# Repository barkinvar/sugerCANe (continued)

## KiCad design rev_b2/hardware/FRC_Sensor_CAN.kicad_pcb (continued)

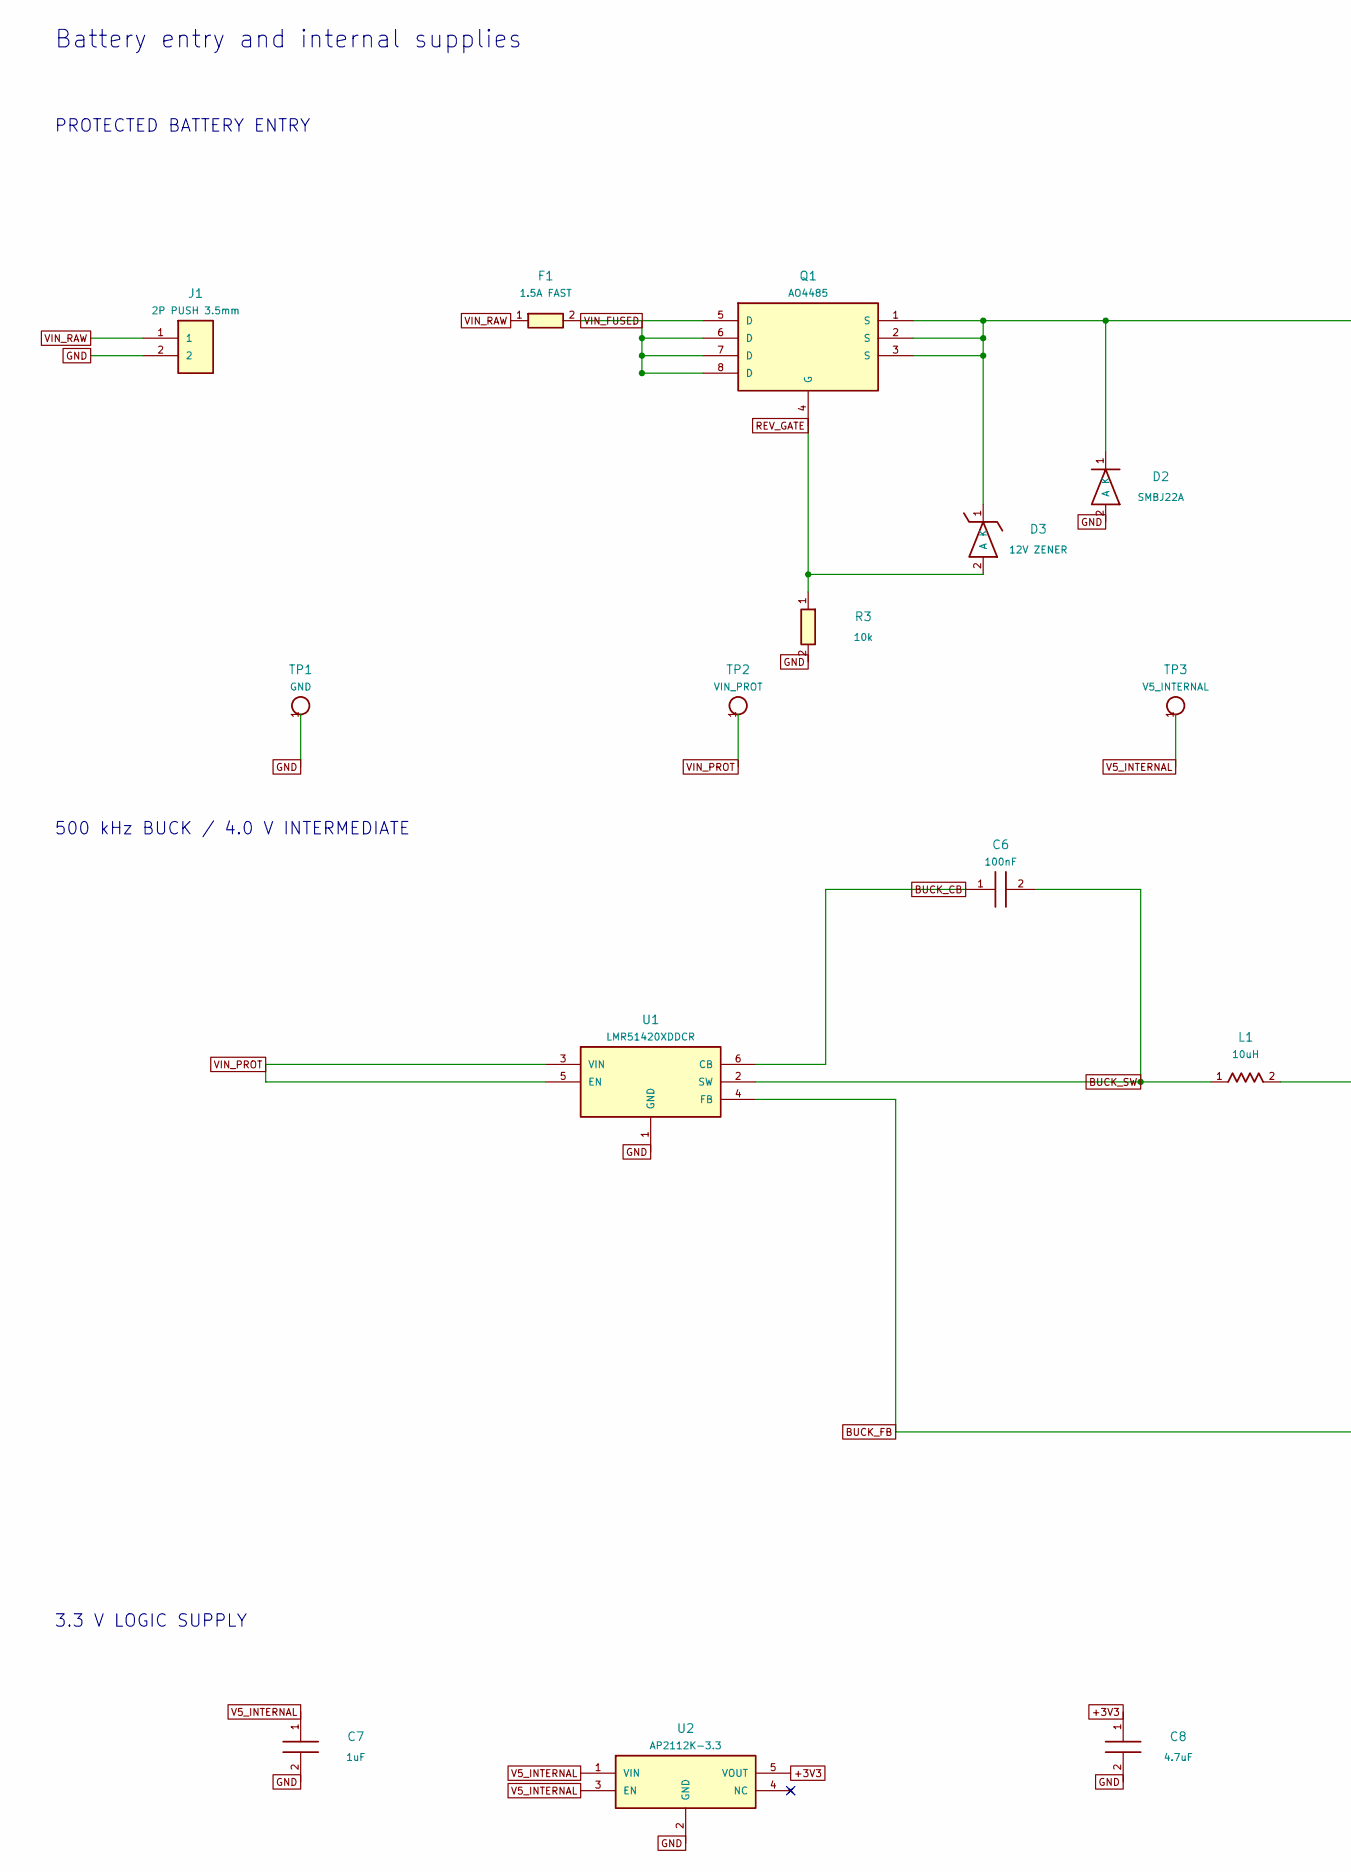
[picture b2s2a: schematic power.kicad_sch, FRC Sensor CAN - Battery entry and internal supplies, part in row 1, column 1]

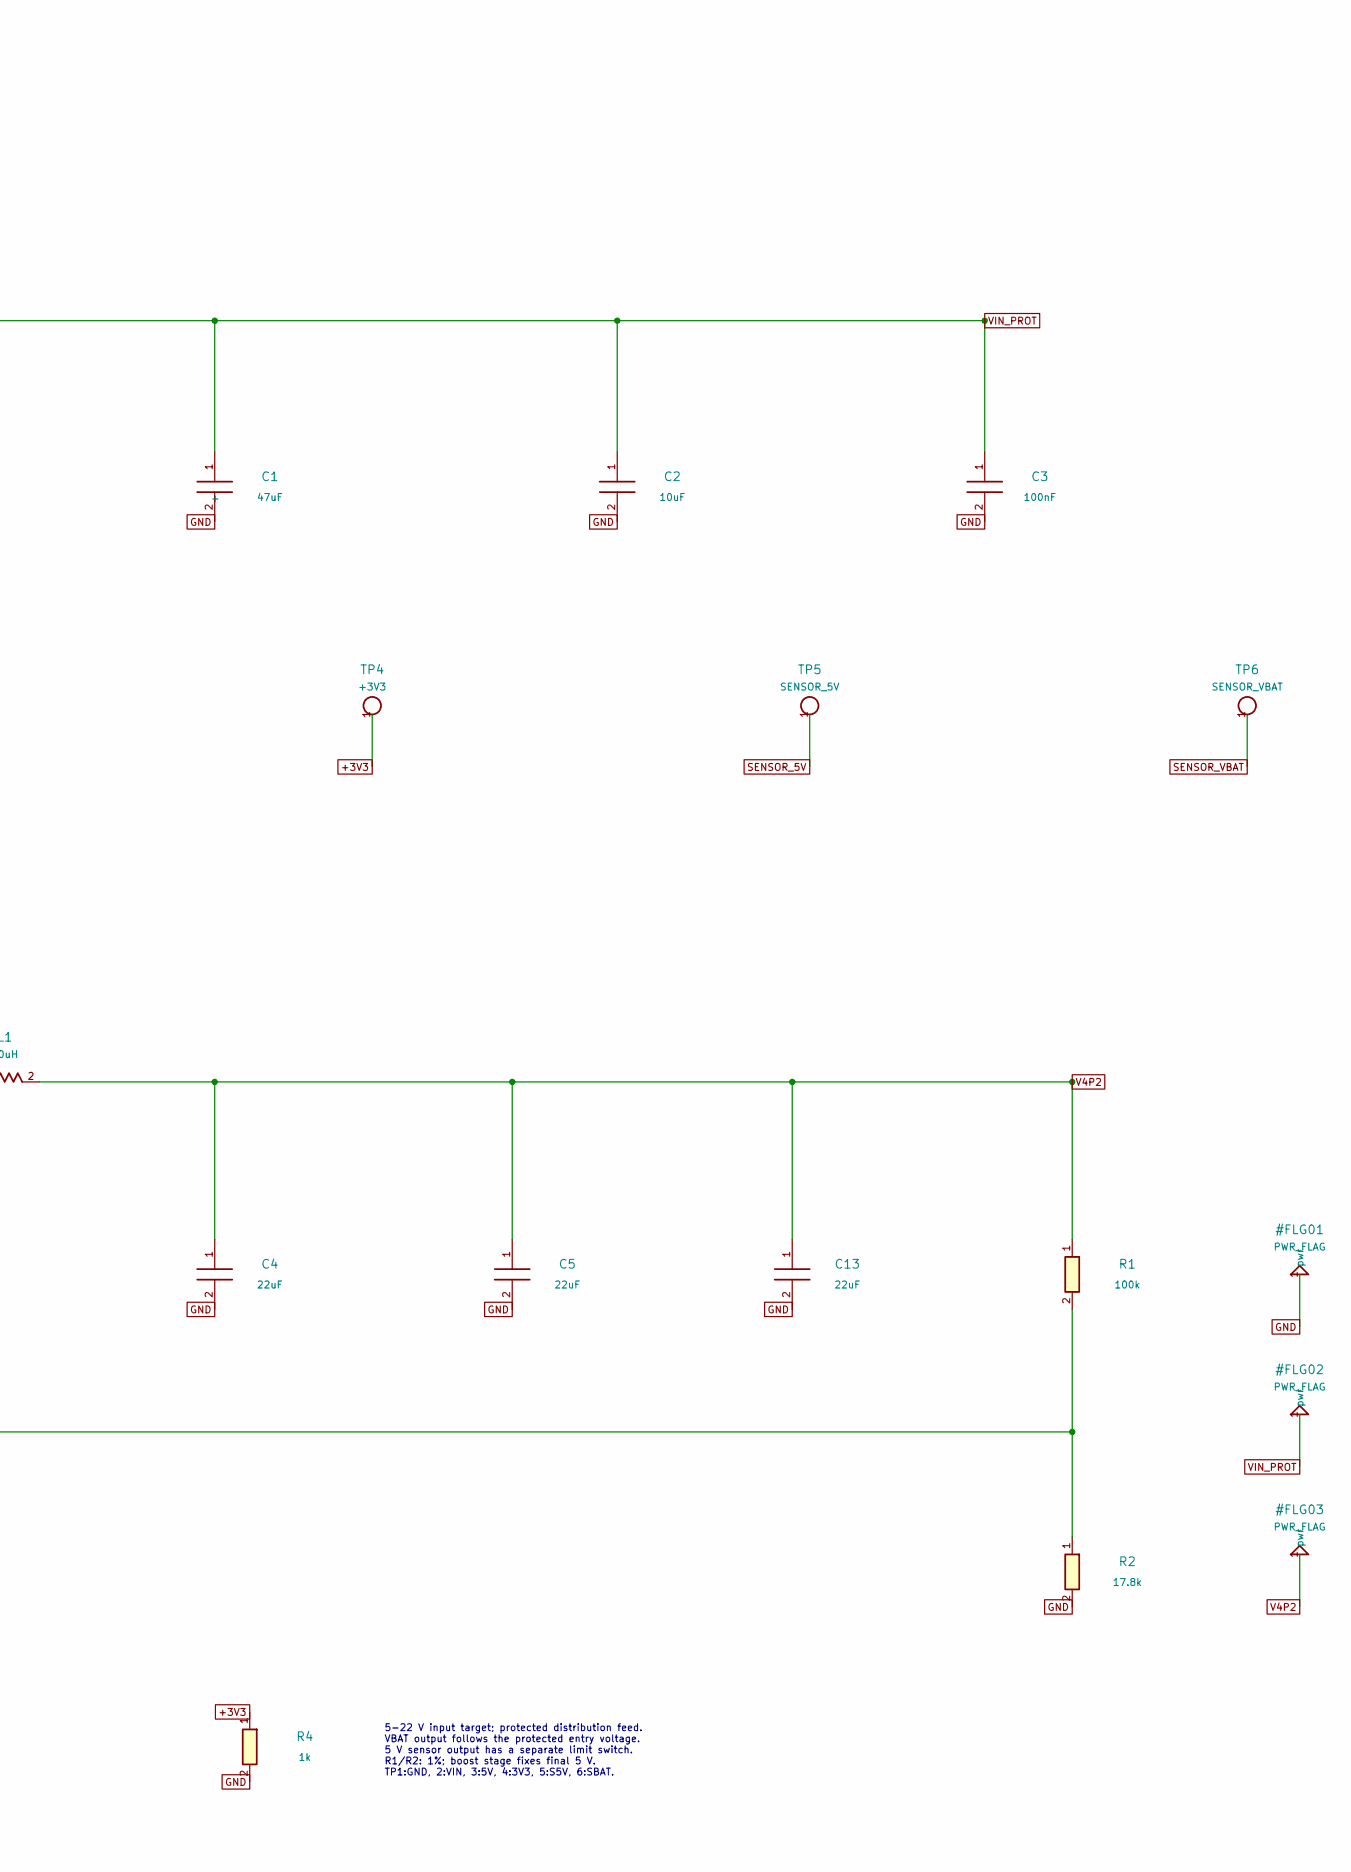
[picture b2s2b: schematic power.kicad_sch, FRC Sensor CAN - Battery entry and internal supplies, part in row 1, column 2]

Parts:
C1: 47uF; CP_Elec_8x6.5; MPN EEE-FK1H470P
C2: 10uF; C_1210_3225Metric; MPN CL32B106KBJNNWE
C3, C6: 100nF; C_0805_2012Metric; MPN CL21B104KCFNNNE
C4, C5, C13: 22uF; C_1206_3216Metric; MPN CL31A226KAHNNNE
C7: 1uF; C_0805_2012Metric; MPN CC0805KKX7R9BB105
C8: 4.7uF; C_0805_2012Metric; MPN TMK212AB7475KG-T
D2: SMBJ22A; D_SMB; MPN SMBJ22A-E3/52
D3: 12V ZENER; D_SOD-123; MPN MMSZ12T1G
F1: 1.5A FAST; Fuse_Littelfuse-NANO2-451_453; MPN 045101.5MRL
J1: 2P PUSH 3.5mm; Weidmuller_LSF_90_2P; MPN 1824420000
L1: 10uH; L_Bourns_SRP7028A_7.3x6.6mm; MPN SRP7028A-100M
Q1: AO4485; SOIC-8_3.9x4.9mm_P1.27mm; MPN AO4485
R1: 100k; R_0805_2012Metric; MPN 0805W8F1003T5E
R2: 17.8k; R_0805_2012Metric; MPN ERJ-6ENF1782V
R3: 10k; R_0805_2012Metric; MPN 0805W8F1002T5E
R4: 1k; R_0805_2012Metric; MPN 0805W8F1001T5E
TP1: GND; TestPoint_Pad_D2.0mm
TP2: VIN_PROT; TestPoint_Pad_D2.0mm
TP3: V5_INTERNAL; TestPoint_Pad_D2.0mm
TP4: +3V3; TestPoint_Pad_D2.0mm
TP5: SENSOR_5V; TestPoint_Pad_D2.0mm
TP6: SENSOR_VBAT; TestPoint_Pad_D2.0mm
U1: LMR51420XDDCR; TSOT-23-6; MPN LMR51420XDDCR
U2: AP2112K-3.3; SOT-23-5; MPN AP2112K-3.3TRG1

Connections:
+3V3: C8.1, R4.1, TP4.1, U2.5 (VOUT); also elsewhere on the board
BUCK_CB: C6.1, U1.6 (CB)
BUCK_FB: R1.2, R2.1, U1.4 (FB)
BUCK_SW: C6.2, L1.1, U1.2 (SW)
GND: C1.2, C2.2, C3.2, C4.2, C5.2, C7.2, C8.2, C13.2, D2.2 (A), J1.2, R2.2, R3.2, R4.2, TP1.1, U1.1 (GND), U2.2 (GND); also elsewhere on the board
REV_GATE: D3.2 (A), Q1.4 (G), R3.1
SENSOR_5V: TP5.1; also elsewhere on the board
SENSOR_VBAT: TP6.1; also elsewhere on the board
V4P2: C4.1, C5.1, C13.1, L1.2, R1.1; also elsewhere on the board
V5_INTERNAL: C7.1, TP3.1, U2.1 (VIN), U2.3 (EN); also elsewhere on the board
VIN_FUSED: F1.2, Q1.5 (D), Q1.6 (D), Q1.7 (D), Q1.8 (D)
VIN_PROT: C1.1 (+), C2.1, C3.1, D2.1 (K), D3.1 (K), Q1.1 (S), Q1.2 (S), Q1.3 (S), TP2.1, U1.3 (VIN), U1.5 (EN); also elsewhere on the board
VIN_RAW: F1.1, J1.1

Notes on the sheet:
Battery entry and internal supplies
PROTECTED BATTERY ENTRY
500 kHz BUCK / 4.0 V INTERMEDIATE
3.3 V LOGIC SUPPLY
5-22 V input target; protected distribution feed. VBAT output follows the protected entry voltage. 5 V sensor output has a separate limit switch. R1/R2: 1%; boost stage fixes final 5 V. TP1:GND, 2:VIN, 3:5V, 4:3V3, 5:S5V, 6:SBAT.

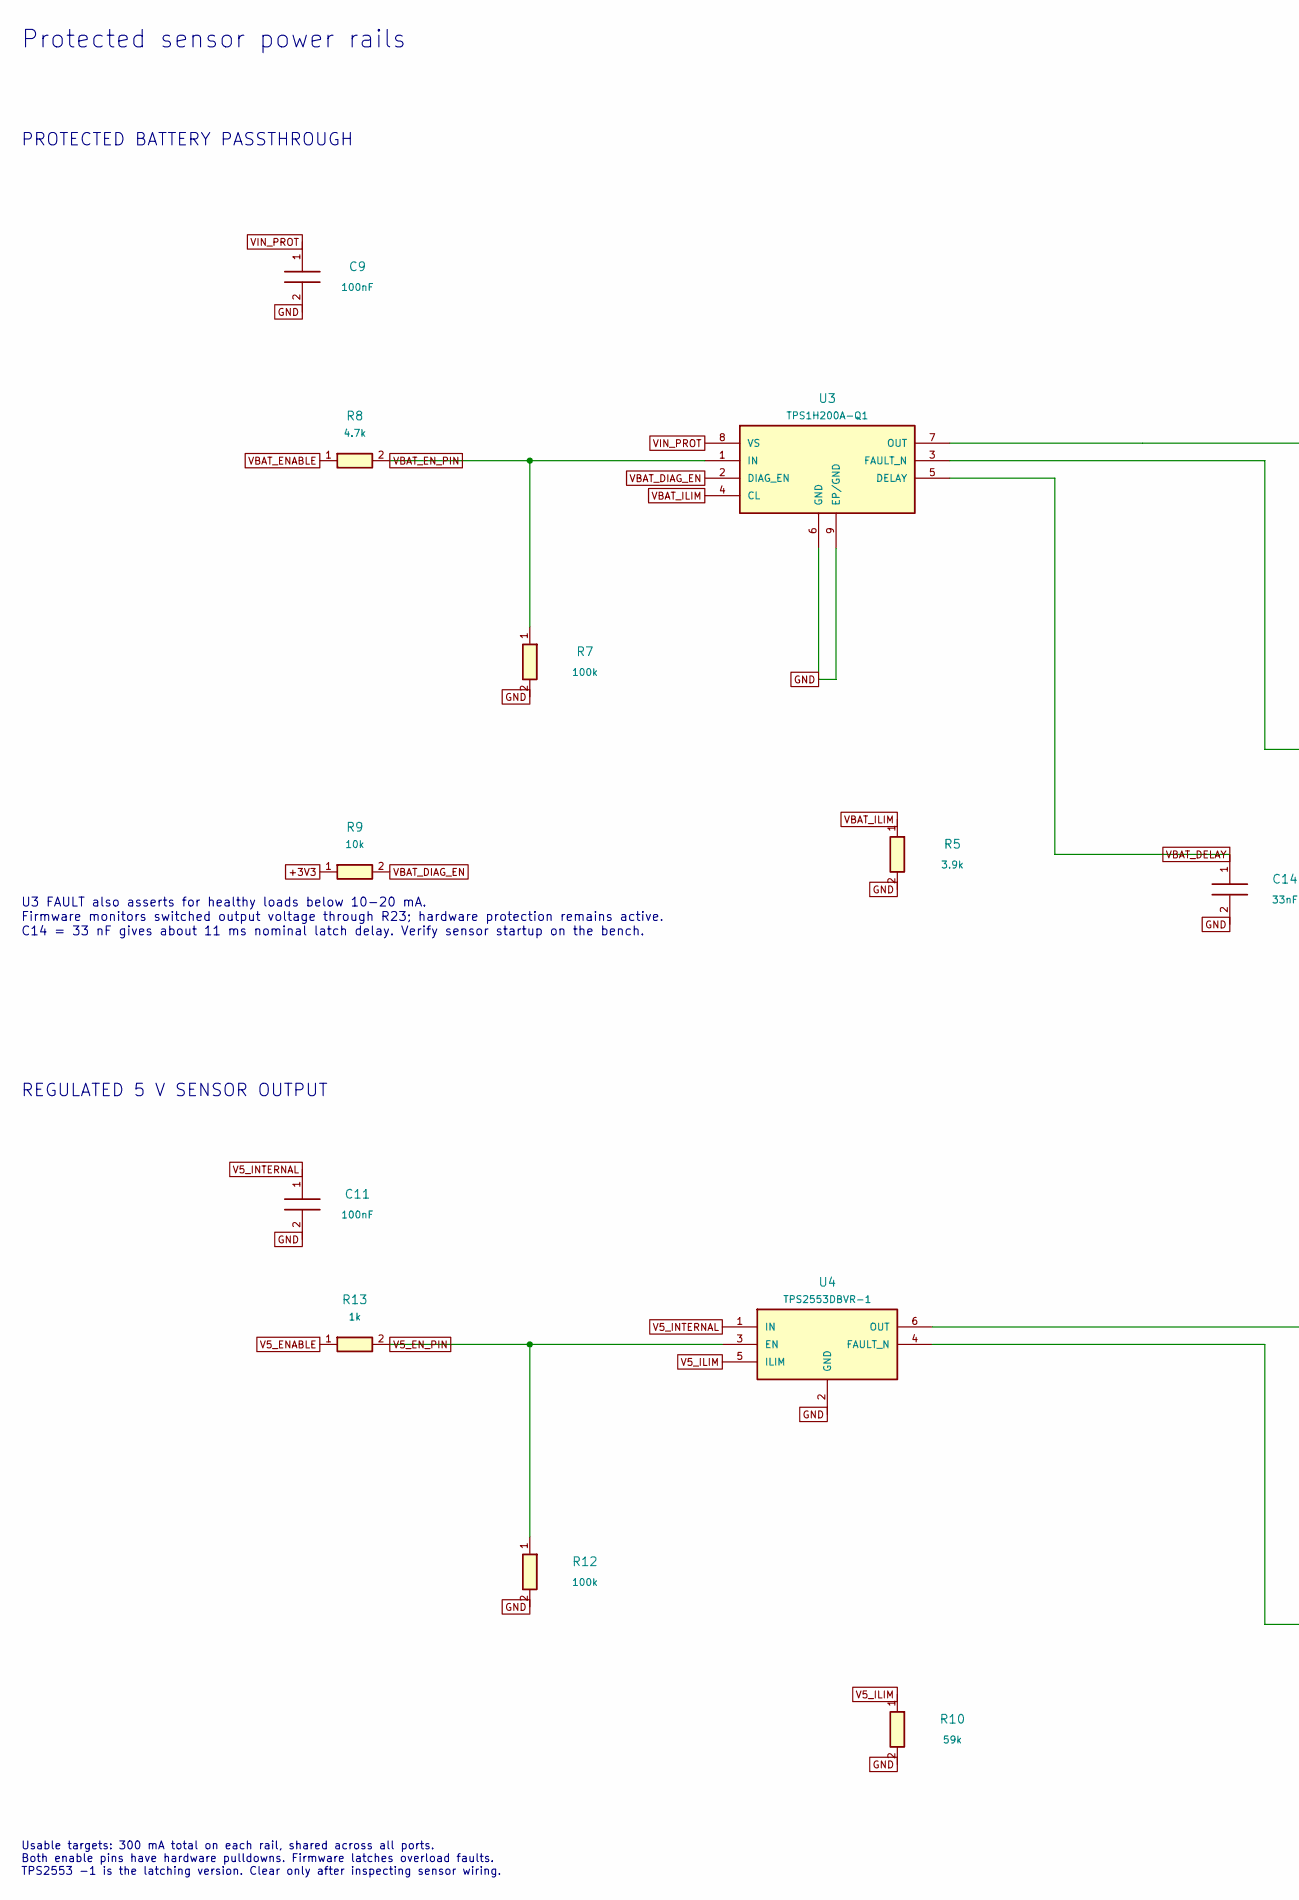
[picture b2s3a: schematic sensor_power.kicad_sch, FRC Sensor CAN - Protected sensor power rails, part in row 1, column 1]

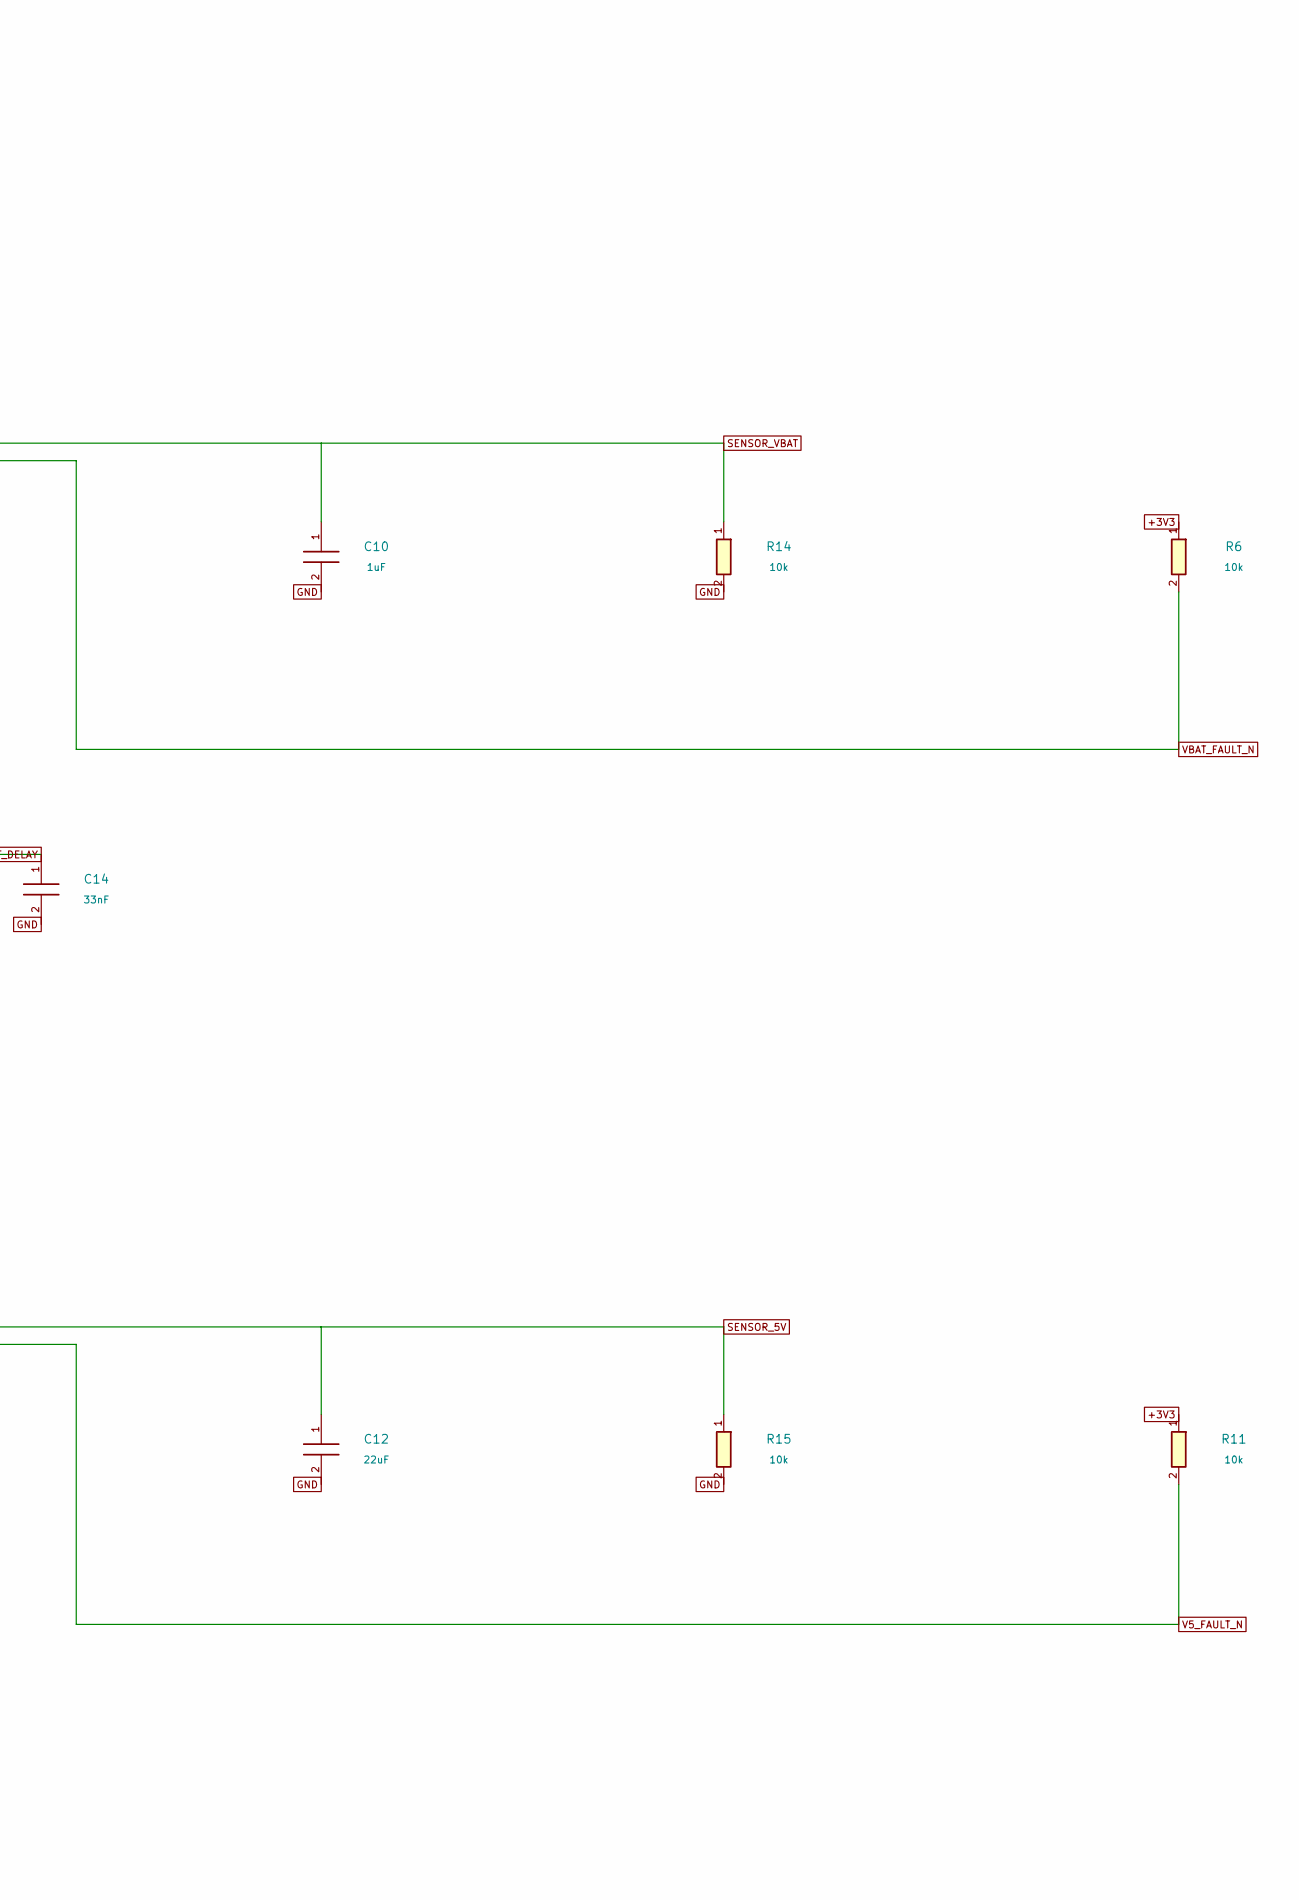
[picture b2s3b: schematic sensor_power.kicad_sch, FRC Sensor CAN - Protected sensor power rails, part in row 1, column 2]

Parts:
C9, C11: 100nF; C_0805_2012Metric; MPN CL21B104KCFNNNE
C10: 1uF; C_0805_2012Metric; MPN CC0805KKX7R9BB105
C12: 22uF; C_1206_3216Metric; MPN CL31A226KAHNNNE
C14: 33nF; C_0805_2012Metric; MPN CC0805KRX7R9BB333
R5: 3.9k; R_0805_2012Metric; MPN RC0805FR-073K9L
R6, R9, R11, R14, R15: 10k; R_0805_2012Metric; MPN 0805W8F1002T5E
R7, R12: 100k; R_0805_2012Metric; MPN 0805W8F1003T5E
R8: 4.7k; R_0805_2012Metric; MPN 0805W8F4701T5E
R10: 59k; R_0805_2012Metric; MPN RC0805FR-0759KL
R13: 1k; R_0805_2012Metric; MPN 0805W8F1001T5E
U3: TPS1H200A-Q1; TI_DGN0008K_HVSSOP8_EP; MPN TPS1H200AQDGNRQ1
U4: TPS2553DBVR-1; SOT-23-6; MPN TPS2553DBVR-1

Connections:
+3V3: R6.1, R9.1, R11.1; also elsewhere on the board
GND: C9.2, C10.2, C11.2, C12.2, C14.2, R5.2, R7.2, R10.2, R12.2, R14.2, R15.2, U3.6 (GND), U3.9 (EP/GND), U4.2 (GND); also elsewhere on the board
SENSOR_5V: C12.1, R15.1, U4.6 (OUT); also elsewhere on the board
SENSOR_VBAT: C10.1, R14.1, U3.7 (OUT); also elsewhere on the board
V5_ENABLE: R13.1; also elsewhere on the board
V5_EN_PIN: R12.1, R13.2, U4.3 (EN)
V5_FAULT_N: R11.2, U4.4 (FAULT_N); also elsewhere on the board
V5_ILIM: R10.1, U4.5 (ILIM)
V5_INTERNAL: C11.1, U4.1 (IN); also elsewhere on the board
VBAT_DELAY: C14.1, U3.5 (DELAY)
VBAT_DIAG_EN: R9.2, U3.2 (DIAG_EN)
VBAT_ENABLE: R8.1; also elsewhere on the board
VBAT_EN_PIN: R7.1, R8.2, U3.1 (IN)
VBAT_FAULT_N: R6.2, U3.3 (FAULT_N); also elsewhere on the board
VBAT_ILIM: R5.1, U3.4 (CL)
VIN_PROT: C9.1, U3.8 (VS); also elsewhere on the board

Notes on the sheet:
Protected sensor power rails
PROTECTED BATTERY PASSTHROUGH
U3 FAULT also asserts for healthy loads below 10-20 mA. Firmware monitors switched output voltage through R23; hardware protection remains active. C14 = 33 nF gives about 11 ms nominal latch delay. Verify sensor startup on the bench.
REGULATED 5 V SENSOR OUTPUT
Usable targets: 300 mA total on each rail, shared across all ports. Both enable pins have hardware pulldowns. Firmware latches overload faults. TPS2553 -1 is the latching version. Clear only after inspecting sensor wiring.

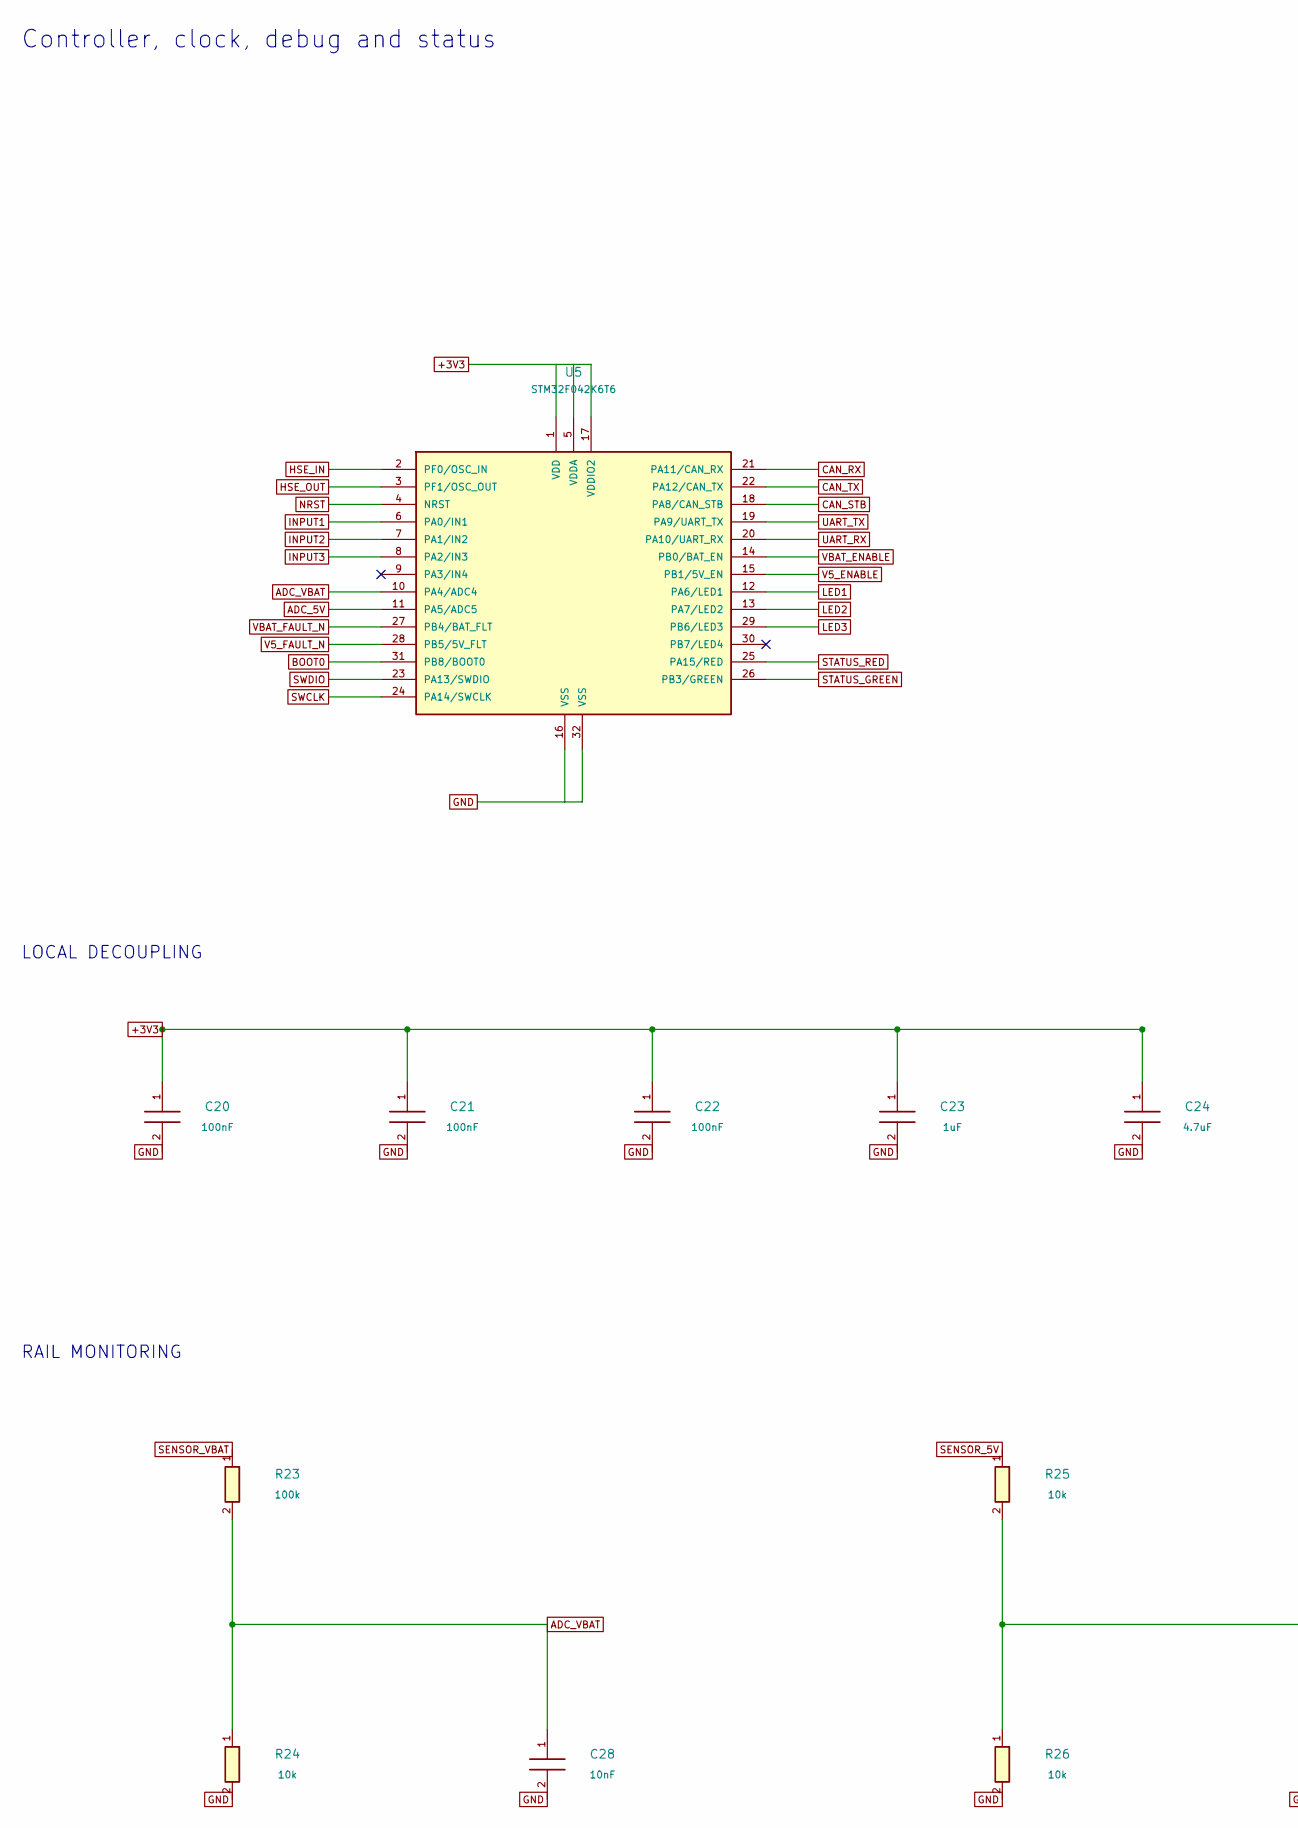
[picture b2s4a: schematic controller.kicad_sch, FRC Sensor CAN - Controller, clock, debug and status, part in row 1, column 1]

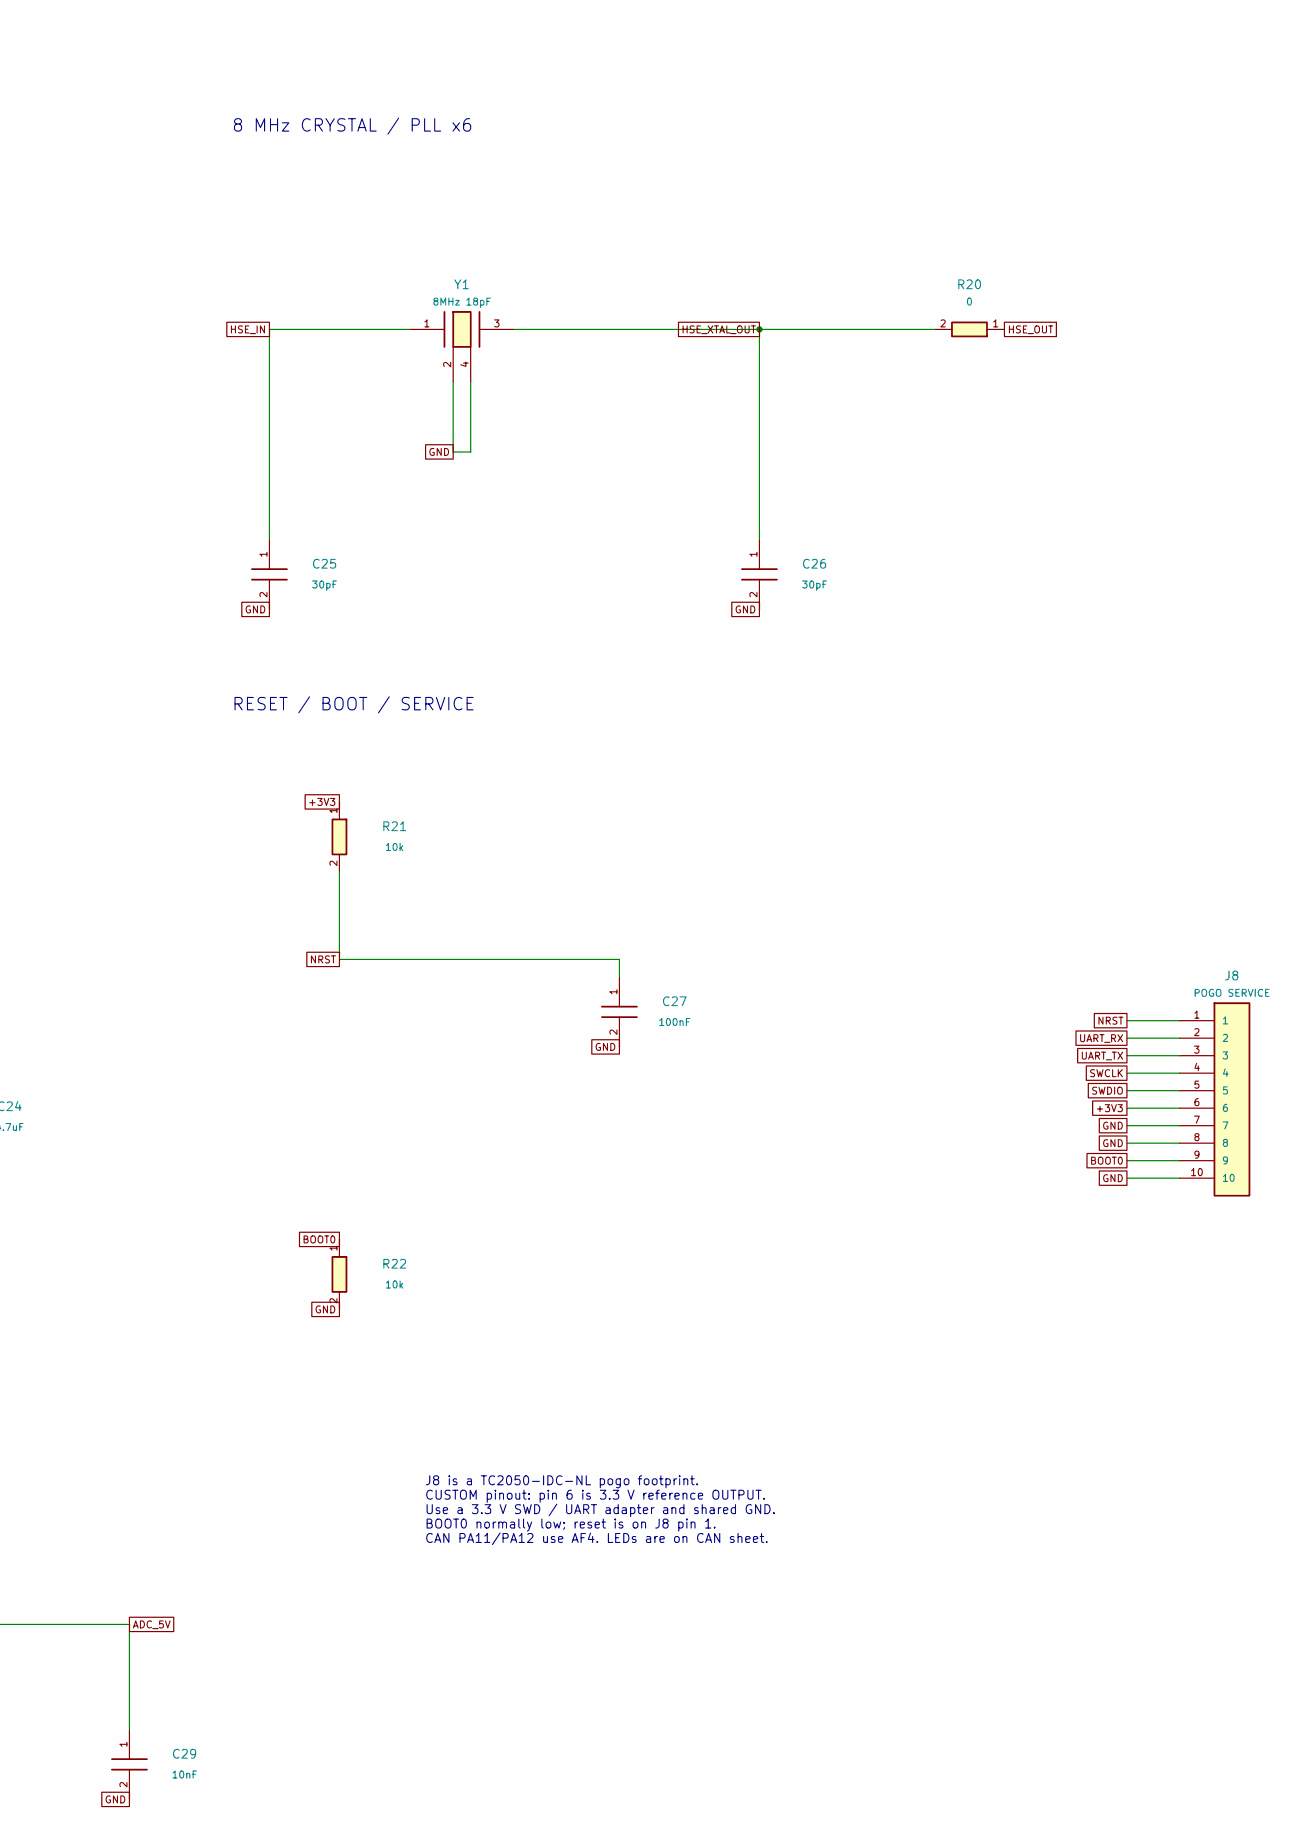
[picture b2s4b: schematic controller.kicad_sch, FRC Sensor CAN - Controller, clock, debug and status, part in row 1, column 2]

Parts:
C20, C21, C22, C27: 100nF; C_0805_2012Metric; MPN CL21B104KCFNNNE
C23: 1uF; C_0805_2012Metric; MPN CC0805KKX7R9BB105
C24: 4.7uF; C_0805_2012Metric; MPN TMK212AB7475KG-T
C25, C26: 30pF; C_0805_2012Metric; MPN C0805C300J5GACTU
C28, C29: 10nF; C_0805_2012Metric; MPN CC0805KRX7R9BB103
J8: POGO SERVICE; Tag-Connect_TC2050-IDC-NL_2x05_P1.27mm_Vertical
R20: 0; R_0805_2012Metric; MPN RC0805JR-070RL
R21, R22, R24, R25, R26: 10k; R_0805_2012Metric; MPN 0805W8F1002T5E
R23: 100k; R_0805_2012Metric; MPN 0805W8F1003T5E
U5: STM32F042K6T6; LQFP-32_7x7mm_P0.8mm; MPN STM32F042K6T6
Y1: 8MHz 18pF; Abracon_ABM3B_5.0x3.2mm; MPN ABM3B-8.000MHZ-B2-T

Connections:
+3V3: C20.1, C21.1, C22.1, C23.1, C24.1, J8.6, R21.1, U5.1 (VDD), U5.5 (VDDA), U5.17 (VDDIO2); also elsewhere on the board
ADC_5V: C29.1, R25.2, R26.1, U5.11 (PA5/ADC5)
ADC_VBAT: C28.1, R23.2, R24.1, U5.10 (PA4/ADC4)
BOOT0: J8.9, R22.1, U5.31 (PB8/BOOT0)
CAN_RX: U5.21 (PA11/CAN_RX); also elsewhere on the board
CAN_STB: U5.18 (PA8/CAN_STB); also elsewhere on the board
CAN_TX: U5.22 (PA12/CAN_TX); also elsewhere on the board
GND: C20.2, C21.2, C22.2, C23.2, C24.2, C25.2, C26.2, C27.2, C28.2, C29.2, J8.7, J8.8, J8.10, R22.2, R24.2, R26.2, U5.16 (VSS), U5.32 (VSS), Y1.2, Y1.4; also elsewhere on the board
HSE_IN: C25.1, U5.2 (PF0/OSC_IN), Y1.1
HSE_OUT: R20.1, U5.3 (PF1/OSC_OUT)
HSE_XTAL_OUT: C26.1, R20.2, Y1.3
INPUT1: U5.6 (PA0/IN1); also elsewhere on the board
INPUT2: U5.7 (PA1/IN2); also elsewhere on the board
INPUT3: U5.8 (PA2/IN3); also elsewhere on the board
LED1: U5.12 (PA6/LED1); also elsewhere on the board
LED2: U5.13 (PA7/LED2); also elsewhere on the board
LED3: U5.29 (PB6/LED3); also elsewhere on the board
NRST: C27.1, J8.1, R21.2, U5.4 (NRST)
SENSOR_5V: R25.1; also elsewhere on the board
SENSOR_VBAT: R23.1; also elsewhere on the board
STATUS_GREEN: U5.26 (PB3/GREEN); also elsewhere on the board
STATUS_RED: U5.25 (PA15/RED); also elsewhere on the board
SWCLK: J8.4, U5.24 (PA14/SWCLK)
SWDIO: J8.5, U5.23 (PA13/SWDIO)
UART_RX: J8.2, U5.20 (PA10/UART_RX)
UART_TX: J8.3, U5.19 (PA9/UART_TX)
V5_ENABLE: U5.15 (PB1/5V_EN); also elsewhere on the board
V5_FAULT_N: U5.28 (PB5/5V_FLT); also elsewhere on the board
VBAT_ENABLE: U5.14 (PB0/BAT_EN); also elsewhere on the board
VBAT_FAULT_N: U5.27 (PB4/BAT_FLT); also elsewhere on the board

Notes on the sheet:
Controller, clock, debug and status
8 MHz CRYSTAL / PLL x6
RESET / BOOT / SERVICE
LOCAL DECOUPLING
RAIL MONITORING
J8 is a TC2050-IDC-NL pogo footprint. CUSTOM pinout: pin 6 is 3.3 V reference OUTPUT. Use a 3.3 V SWD / UART adapter and shared GND. BOOT0 normally low; reset is on J8 pin 1. CAN PA11/PA12 use AF4. LEDs are on CAN sheet.
